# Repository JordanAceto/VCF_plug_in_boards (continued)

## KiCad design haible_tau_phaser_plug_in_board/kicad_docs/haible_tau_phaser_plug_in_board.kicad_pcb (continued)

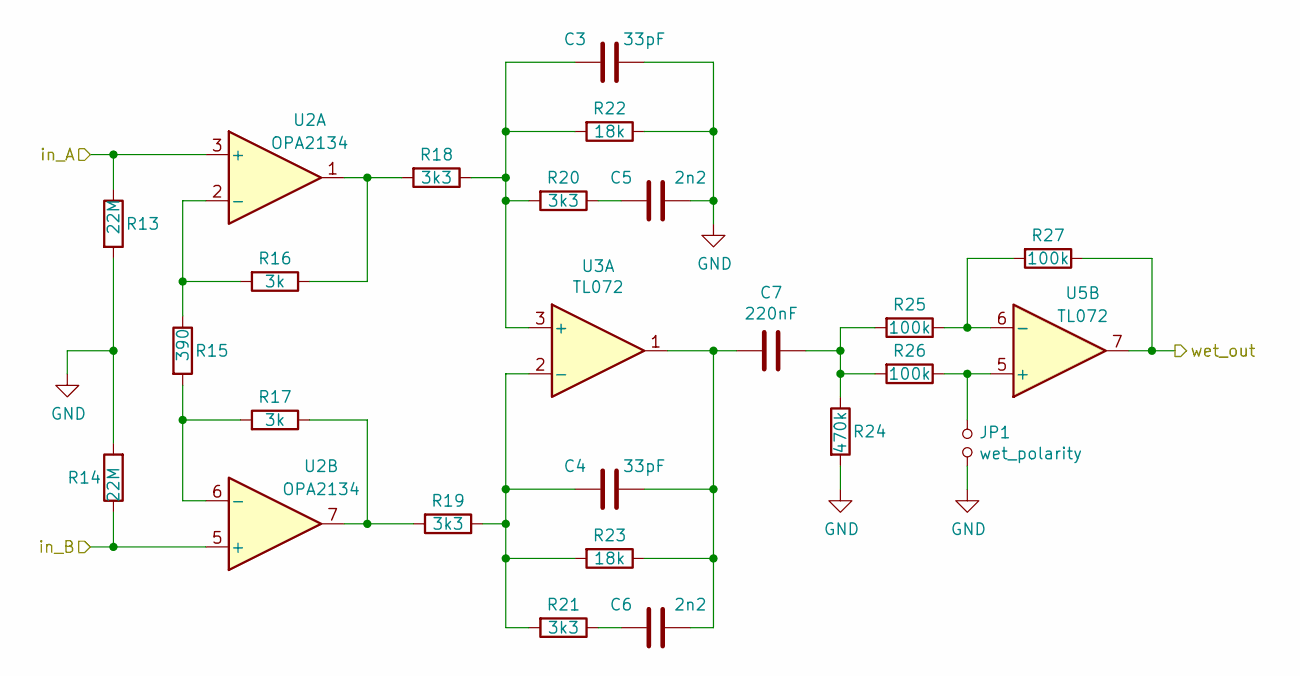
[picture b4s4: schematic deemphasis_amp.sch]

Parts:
C3, C4: 33pF; C_0805_2012Metric_Pad1.15x1.40mm_HandSolder
C5, C6: 2n2; C_0805_2012Metric_Pad1.15x1.40mm_HandSolder
C7: 220nF; C_0805_2012Metric_Pad1.15x1.40mm_HandSolder
JP1: wet_polarity; SolderJumper-2_P1.3mm_Open_Pad1.0x1.5mm
R13, R14: 22M; R_0805_2012Metric_Pad1.15x1.40mm_HandSolder
R15: 390; R_0805_2012Metric_Pad1.15x1.40mm_HandSolder
R16, R17: 3k; R_0805_2012Metric_Pad1.15x1.40mm_HandSolder
R18, R19, R20, R21: 3k3; R_0805_2012Metric_Pad1.15x1.40mm_HandSolder
R22, R23: 18k; R_0805_2012Metric_Pad1.15x1.40mm_HandSolder
R24: 470k; R_0805_2012Metric_Pad1.15x1.40mm_HandSolder
R25, R26, R27: 100k; R_0805_2012Metric_Pad1.15x1.40mm_HandSolder
U2: OPA2134; SOIC-8_3.9x4.9mm_P1.27mm
U3, U5: TL072; SOIC-8_3.9x4.9mm_P1.27mm

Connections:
/cv_processor/control_out_A: R13.1, U2.3 (+); also elsewhere on the board
/cv_processor/control_out_B: R14.1, U2.5 (+); also elsewhere on the board
/feedback_VCA/feedback_signal_in: R27.1, U5.7; also elsewhere on the board
GND: C3.1, C5.1, JP1.2, R13.2, R14.2, R22.1, R24.2; also elsewhere on the board
unnamed: C3.2, R18.1, R20.2, R22.2, U3.3 (+)
unnamed: C4.1, C6.1, C7.2, R23.1, U3.1
unnamed: C4.2, R19.1, R21.2, R23.2, U3.2 (-)
unnamed: C5.2, R20.1
unnamed: C6.2, R21.1
unnamed: C7.1, R24.1, R25.2, R26.2
unnamed: JP1.1, R26.1, U5.5 (+)
unnamed: R15.1, R16.2, U2.2 (-)
unnamed: R15.2, R17.2, U2.6 (-)
unnamed: R16.1, R18.2, U2.1
unnamed: R17.1, R19.2, U2.7
unnamed: R25.1, R27.2, U5.6 (-)

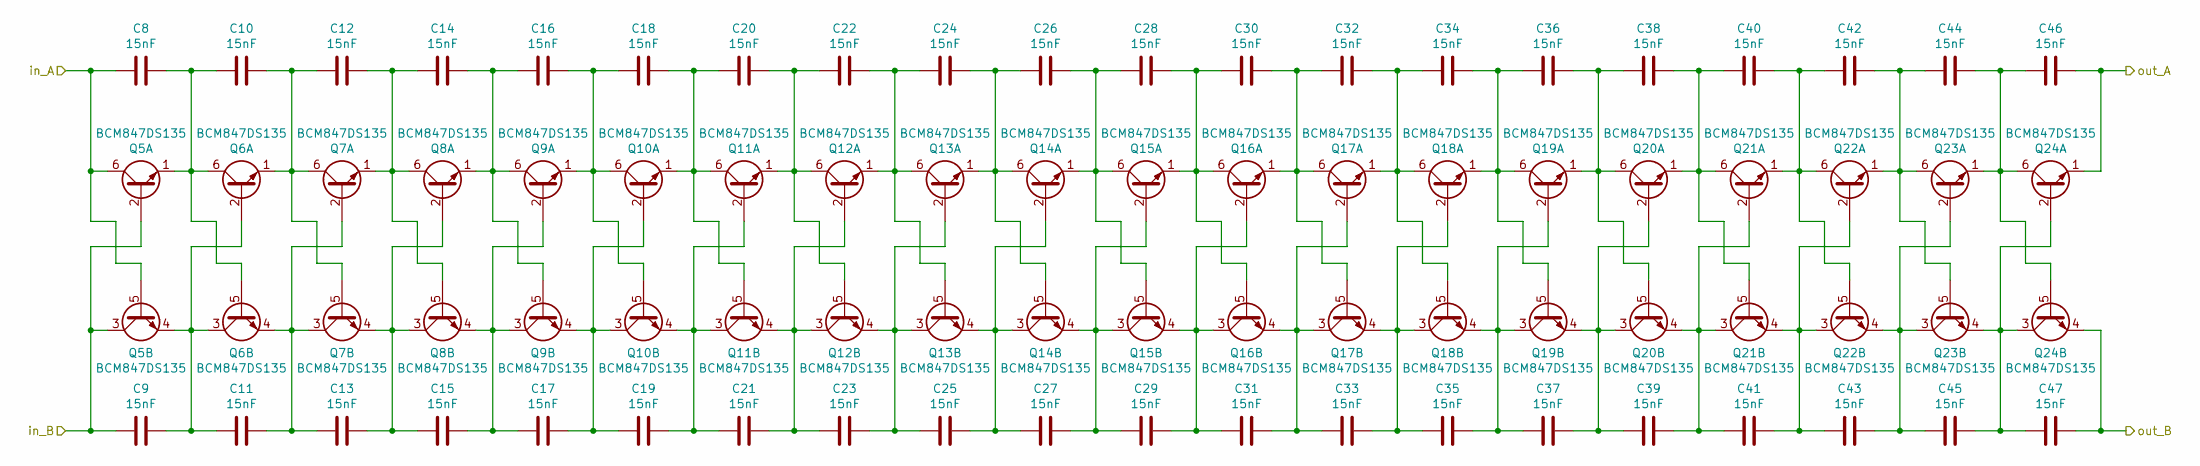
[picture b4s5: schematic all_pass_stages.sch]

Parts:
C8, C9, C10, C11, C12, C13, C14, C15, C16, C17, C18, C19, C20, C21, C22, C23, C24, C25, C26, C27, C28, C29, C30, C31, C32, C33, C34, C35, C36, C37, C38, C39, C40, C41, C42, C43, C44, C45, C46, C47: 15nF; C_0805_2012Metric_Pad1.15x1.40mm_HandSolder
Q5, Q6, Q7, Q8, Q9, Q10, Q11, Q12, Q13, Q14, Q15, Q16, Q17, Q18, Q19, Q20, Q21, Q22, Q23, Q24: BCM847DS135; SOT457

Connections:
/all_pass_stages/in_A: C8.2, Q5.5 (B), Q5.6 (C); also elsewhere on the board
/all_pass_stages/in_B: C9.2, Q5.2 (B), Q5.3 (C); also elsewhere on the board
/cv_processor/control_out_A: C46.1, Q24.1 (E); also elsewhere on the board
/cv_processor/control_out_B: C47.1, Q24.4 (E); also elsewhere on the board
unnamed: C10.1, C12.2, Q6.1 (E), Q7.5 (B), Q7.6 (C)
unnamed: C8.1, C10.2, Q5.1 (E), Q6.5 (B), Q6.6 (C)
unnamed: C11.1, C13.2, Q6.4 (E), Q7.2 (B), Q7.3 (C)
unnamed: C9.1, C11.2, Q5.4 (E), Q6.2 (B), Q6.3 (C)
unnamed: C12.1, C14.2, Q7.1 (E), Q8.5 (B), Q8.6 (C)
unnamed: C13.1, C15.2, Q7.4 (E), Q8.2 (B), Q8.3 (C)
unnamed: C14.1, C16.2, Q8.1 (E), Q9.5 (B), Q9.6 (C)
unnamed: C15.1, C17.2, Q8.4 (E), Q9.2 (B), Q9.3 (C)
unnamed: C16.1, C18.2, Q9.1 (E), Q10.5 (B), Q10.6 (C)
unnamed: C17.1, C19.2, Q9.4 (E), Q10.2 (B), Q10.3 (C)
unnamed: C18.1, C20.2, Q10.1 (E), Q11.5 (B), Q11.6 (C)
unnamed: C19.1, C21.2, Q10.4 (E), Q11.2 (B), Q11.3 (C)
unnamed: C20.1, C22.2, Q11.1 (E), Q12.5 (B), Q12.6 (C)
unnamed: C21.1, C23.2, Q11.4 (E), Q12.2 (B), Q12.3 (C)
unnamed: C22.1, C24.2, Q12.1 (E), Q13.5 (B), Q13.6 (C)
unnamed: C23.1, C25.2, Q12.4 (E), Q13.2 (B), Q13.3 (C)
unnamed: C24.1, C26.2, Q13.1 (E), Q14.5 (B), Q14.6 (C)
unnamed: C25.1, C27.2, Q13.4 (E), Q14.2 (B), Q14.3 (C)
unnamed: C26.1, C28.2, Q14.1 (E), Q15.5 (B), Q15.6 (C)
unnamed: C27.1, C29.2, Q14.4 (E), Q15.2 (B), Q15.3 (C)
unnamed: C28.1, C30.2, Q15.1 (E), Q16.5 (B), Q16.6 (C)
unnamed: C29.1, C31.2, Q15.4 (E), Q16.2 (B), Q16.3 (C)
unnamed: C30.1, C32.2, Q16.1 (E), Q17.5 (B), Q17.6 (C)
unnamed: C31.1, C33.2, Q16.4 (E), Q17.2 (B), Q17.3 (C)
unnamed: C32.1, C34.2, Q17.1 (E), Q18.5 (B), Q18.6 (C)
unnamed: C33.1, C35.2, Q17.4 (E), Q18.2 (B), Q18.3 (C)
unnamed: C34.1, C36.2, Q18.1 (E), Q19.5 (B), Q19.6 (C)
unnamed: C35.1, C37.2, Q18.4 (E), Q19.2 (B), Q19.3 (C)
unnamed: C36.1, C38.2, Q19.1 (E), Q20.5 (B), Q20.6 (C)
unnamed: C37.1, C39.2, Q19.4 (E), Q20.2 (B), Q20.3 (C)
unnamed: C38.1, C40.2, Q20.1 (E), Q21.5 (B), Q21.6 (C)
unnamed: C39.1, C41.2, Q20.4 (E), Q21.2 (B), Q21.3 (C)
unnamed: C40.1, C42.2, Q21.1 (E), Q22.5 (B), Q22.6 (C)
unnamed: C41.1, C43.2, Q21.4 (E), Q22.2 (B), Q22.3 (C)
unnamed: C42.1, C44.2, Q22.1 (E), Q23.5 (B), Q23.6 (C)
unnamed: C43.1, C45.2, Q22.4 (E), Q23.2 (B), Q23.3 (C)
unnamed: C44.1, C46.2, Q23.1 (E), Q24.5 (B), Q24.6 (C)
unnamed: C45.1, C47.2, Q23.4 (E), Q24.2 (B), Q24.3 (C)

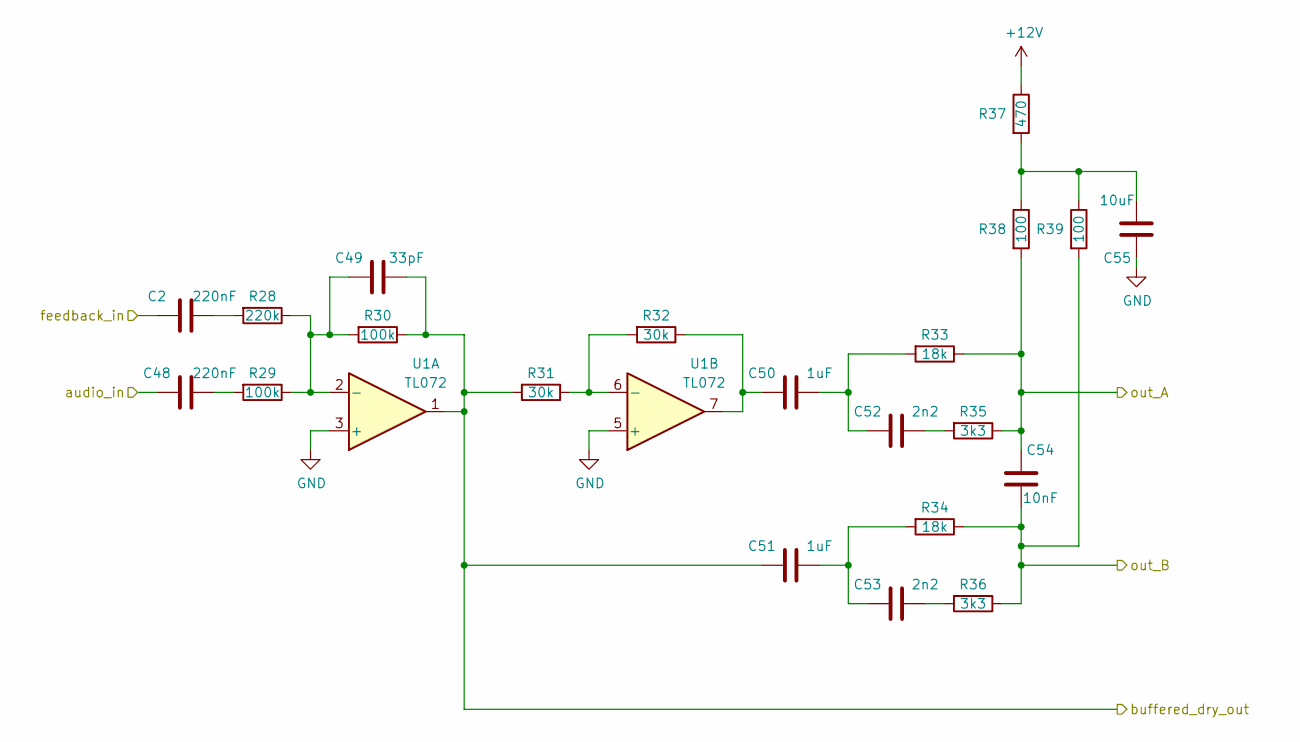
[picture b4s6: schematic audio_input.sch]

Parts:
C2, C48: 220nF; C_0805_2012Metric_Pad1.15x1.40mm_HandSolder
C49: 33pF; C_0805_2012Metric_Pad1.15x1.40mm_HandSolder
C50, C51: 1uF; C_0805_2012Metric_Pad1.15x1.40mm_HandSolder
C52, C53: 2n2; C_0805_2012Metric_Pad1.15x1.40mm_HandSolder
C54: 10nF; C_0805_2012Metric_Pad1.15x1.40mm_HandSolder
C55: 10uF; C_0805_2012Metric_Pad1.15x1.40mm_HandSolder
R28: 220k; R_0805_2012Metric_Pad1.15x1.40mm_HandSolder
R29, R30: 100k; R_0805_2012Metric_Pad1.15x1.40mm_HandSolder
R31, R32: 30k; R_0805_2012Metric_Pad1.15x1.40mm_HandSolder
R33, R34: 18k; R_0805_2012Metric_Pad1.15x1.40mm_HandSolder
R35, R36: 3k3; R_0805_2012Metric_Pad1.15x1.40mm_HandSolder
R37: 470; R_0805_2012Metric_Pad1.15x1.40mm_HandSolder
R38, R39: 100; R_0805_2012Metric_Pad1.15x1.40mm_HandSolder
U1: TL072; SOIC-8_3.9x4.9mm_P1.27mm

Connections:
+12V: R37.1; also elsewhere on the board
/all_pass_stages/in_A: C54.1, R33.1, R35.1, R38.2; also elsewhere on the board
/all_pass_stages/in_B: C54.2, R34.1, R36.1, R39.2; also elsewhere on the board
/audio_input/audio_in: C48.2; also elsewhere on the board
/audio_input/buffered_dry_out: C49.1, C51.2, R30.1, R31.2, U1.1; also elsewhere on the board
/audio_input/feedback_in: C2.2; also elsewhere on the board
GND: C55.2, U1.3 (+), U1.5 (+); also elsewhere on the board
unnamed: C2.1, R28.2
unnamed: C48.1, R29.2
unnamed: C49.2, R28.1, R29.1, R30.2, U1.2 (-)
unnamed: C50.1, C52.2, R33.2
unnamed: C50.2, R32.1, U1.7
unnamed: C51.1, C53.2, R34.2
unnamed: C52.1, R35.2
unnamed: C53.1, R36.2
unnamed: C55.1, R37.2, R38.1, R39.1
unnamed: R31.1, R32.2, U1.6 (-)

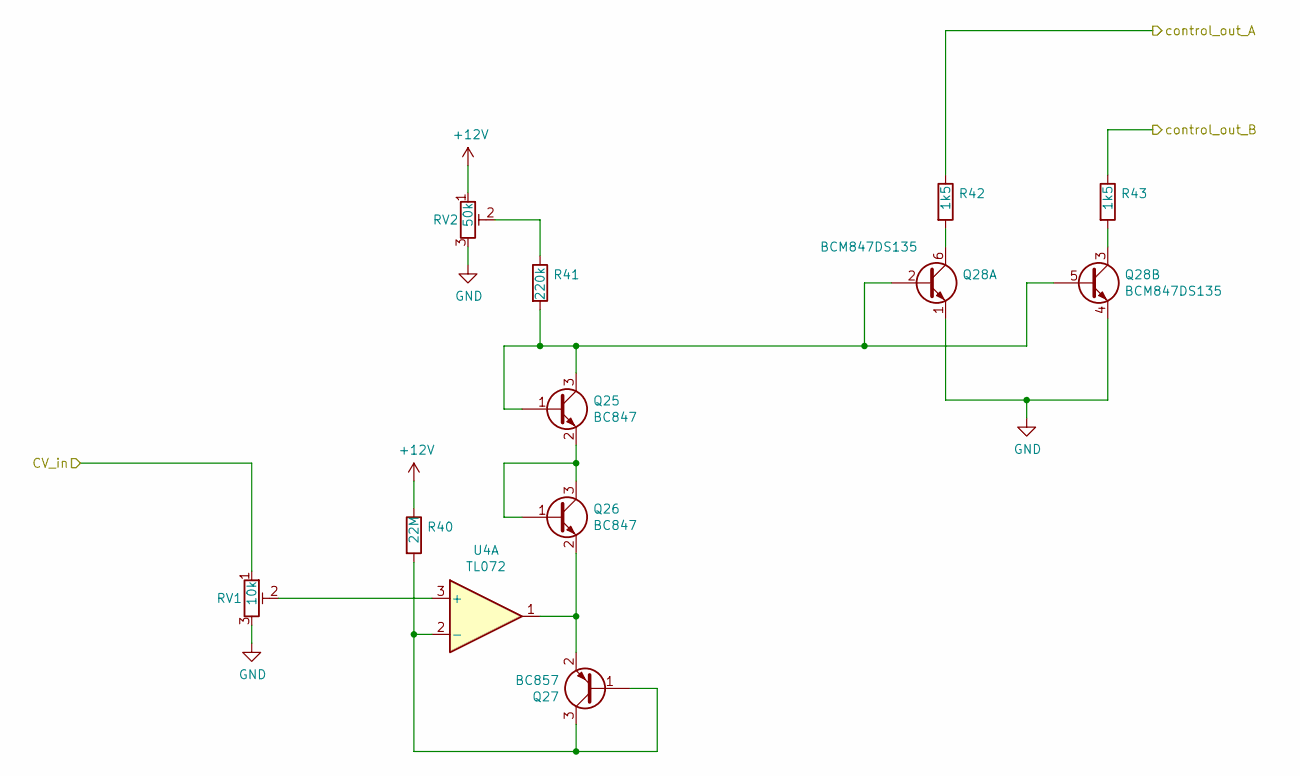
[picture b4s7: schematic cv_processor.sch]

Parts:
Q25, Q26: BC847; SOT-23_Handsoldering
Q27: BC857; SOT-23_Handsoldering
Q28: BCM847DS135; SOT457
R40: 22M; R_0805_2012Metric_Pad1.15x1.40mm_HandSolder
R41: 220k; R_0805_2012Metric_Pad1.15x1.40mm_HandSolder
R42, R43: 1k5; R_0805_2012Metric_Pad1.15x1.40mm_HandSolder
RV1: 10k; Potentiometer_Bourns_3269W_Vertical
RV2: 50k; Potentiometer_Bourns_3269W_Vertical
U4: TL072; SOIC-8_3.9x4.9mm_P1.27mm

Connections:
+12V: R40.1, RV2.1; also elsewhere on the board
/cv_processor/CV_in: RV1.1; also elsewhere on the board
/cv_processor/control_out_A: R42.1; also elsewhere on the board
/cv_processor/control_out_B: R43.1; also elsewhere on the board
GND: Q28.1 (E), Q28.4 (E), RV1.3, RV2.3; also elsewhere on the board
unnamed: Q25.1 (B), Q25.3 (C), Q28.2 (B), Q28.5 (B), R41.2
unnamed: Q25.2 (E), Q26.1 (B), Q26.3 (C)
unnamed: Q26.2 (E), Q27.2 (E), U4.1
unnamed: Q27.1 (B), Q27.3 (C), R40.2, U4.2 (-)
unnamed: Q28.3 (C), R43.2
unnamed: Q28.6 (C), R42.2
unnamed: R41.1, RV2.2
unnamed: RV1.2, U4.3 (+)

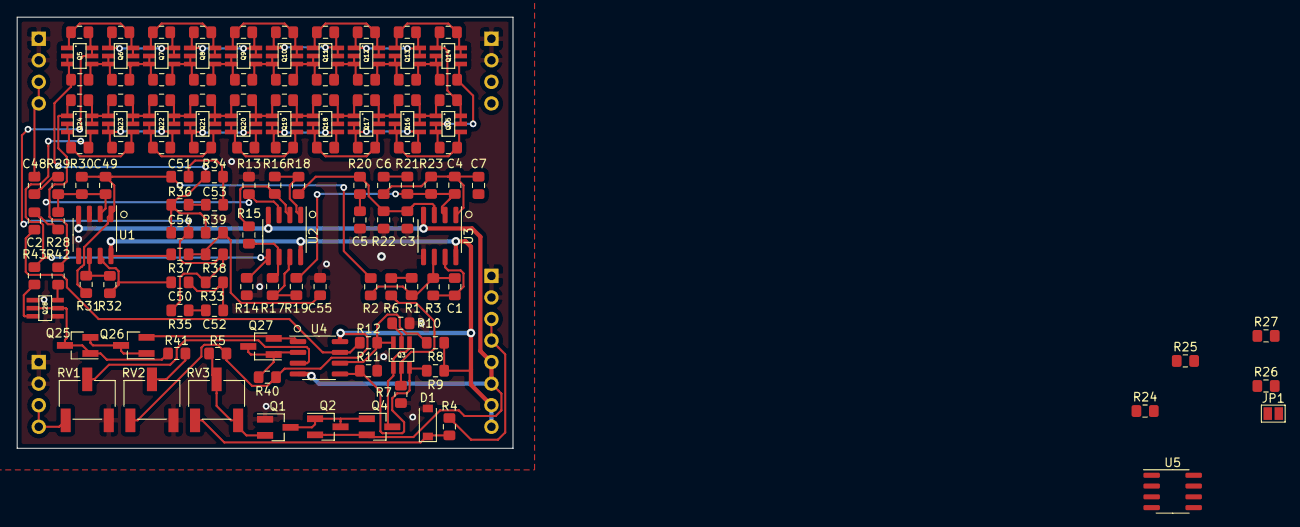
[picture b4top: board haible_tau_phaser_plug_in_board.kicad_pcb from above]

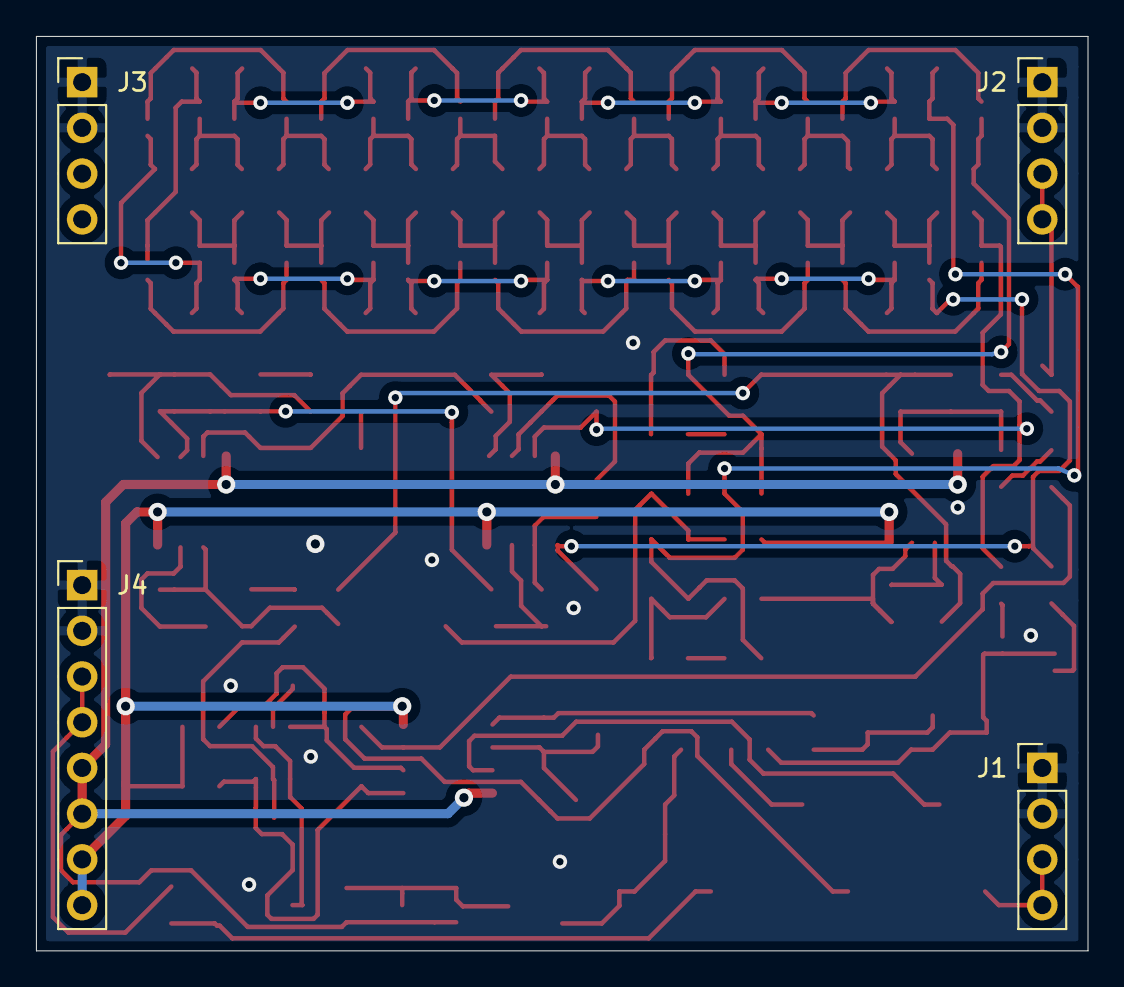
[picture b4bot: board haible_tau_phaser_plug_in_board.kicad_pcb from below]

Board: 2 copper layers, 58.4 x 50.8 mm, 140 parts (4 on the bottom side), 91 nets.

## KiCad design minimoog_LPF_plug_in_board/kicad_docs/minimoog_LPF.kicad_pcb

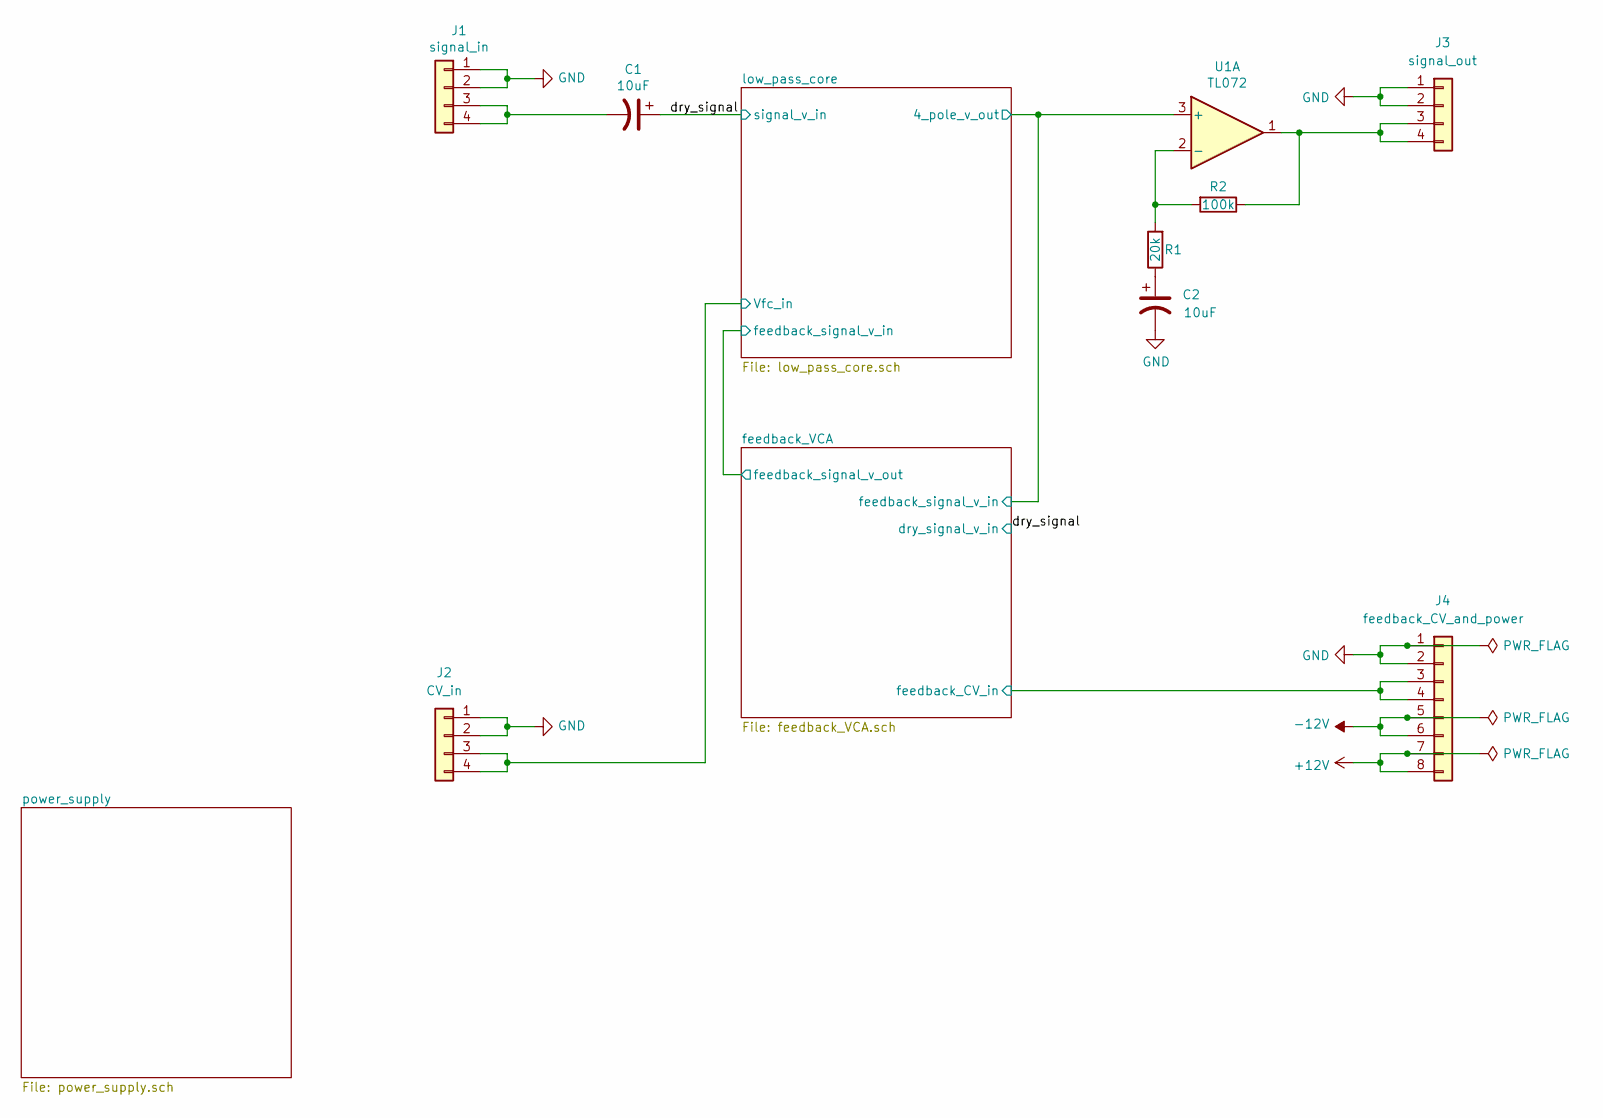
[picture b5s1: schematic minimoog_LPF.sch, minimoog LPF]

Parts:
C1, C2: 10uF; CP_Radial_D6.3mm_P2.50mm
J1: signal_in; PinHeader_1x04_P2.54mm_Vertical
J2: CV_in; PinHeader_1x04_P2.54mm_Vertical
J3: signal_out; PinHeader_1x04_P2.54mm_Vertical
J4: feedback_CV_and_power; PinHeader_1x08_P2.54mm_Vertical
R1: 20k; R_0805_2012Metric_Pad1.15x1.40mm_HandSolder
R2: 100k; R_0805_2012Metric_Pad1.15x1.40mm_HandSolder
U1: TL072; SOIC-8_3.9x4.9mm_P1.27mm

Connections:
+12V: J4.7, J4.8; also elsewhere on the board
-12V: J4.5, J4.6; also elsewhere on the board
/dry_signal: C1.1; also elsewhere on the board
/feedback_VCA/feedback_CV_in: J4.3, J4.4; also elsewhere on the board
/low_pass_core/4_pole_v_out: U1.3 (+); also elsewhere on the board
/low_pass_core/Vfc_in: J2.3, J2.4; also elsewhere on the board
GND: C2.2, J1.1, J1.2, J2.1, J2.2, J3.1, J3.2, J4.1, J4.2; also elsewhere on the board
unnamed: C1.2, J1.3, J1.4
unnamed: C2.1, R1.1
unnamed: J3.3, J3.4, R2.1, U1.1
unnamed: R1.2, R2.2, U1.2 (-)

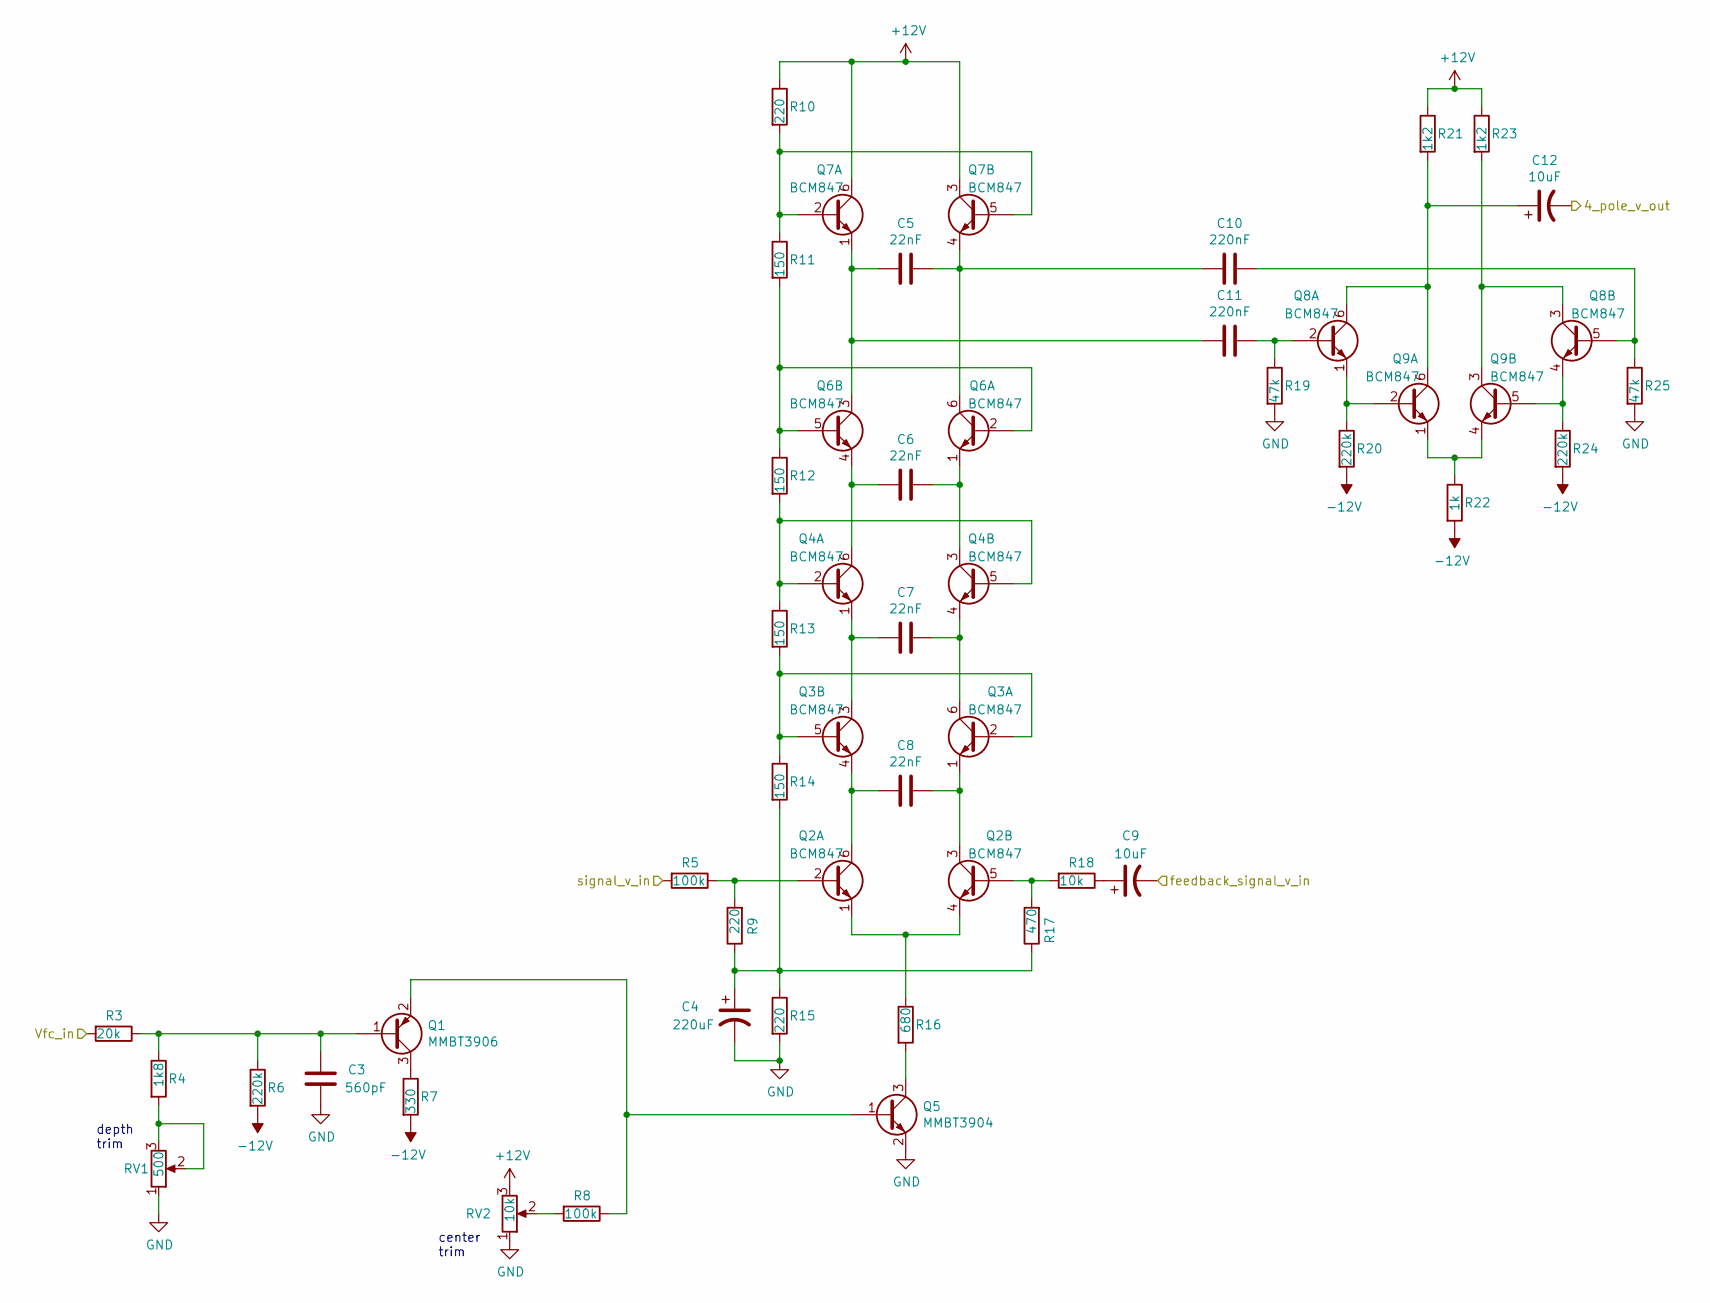
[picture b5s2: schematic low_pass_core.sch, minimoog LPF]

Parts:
C3: 560pF; C_0805_2012Metric_Pad1.15x1.40mm_HandSolder
C4: 220uF; CP_Radial_D6.3mm_P2.50mm
C5, C6, C7, C8: 22nF; C_0805_2012Metric_Pad1.15x1.40mm_HandSolder
C9, C12: 10uF; CP_Radial_D6.3mm_P2.50mm
C10, C11: 220nF; C_Rect_L7.0mm_W3.5mm_P5.00mm
Q1: MMBT3906; SOT-23_Handsoldering
Q2, Q3, Q4, Q6, Q7, Q8, Q9: BCM847; SOT457
Q5: MMBT3904; SOT-23_Handsoldering
R3: 20k; R_0805_2012Metric_Pad1.15x1.40mm_HandSolder
R4: 1k8; R_0805_2012Metric_Pad1.15x1.40mm_HandSolder
R5, R8: 100k; R_0805_2012Metric_Pad1.15x1.40mm_HandSolder
R6, R20, R24: 220k; R_0805_2012Metric_Pad1.15x1.40mm_HandSolder
R7: 330; R_0805_2012Metric_Pad1.15x1.40mm_HandSolder
R9, R10, R15: 220; R_0805_2012Metric_Pad1.15x1.40mm_HandSolder
R11, R12, R13, R14: 150; R_0805_2012Metric_Pad1.15x1.40mm_HandSolder
R16: 680; R_0805_2012Metric_Pad1.15x1.40mm_HandSolder
R17: 470; R_0805_2012Metric_Pad1.15x1.40mm_HandSolder
R18: 10k; R_0805_2012Metric_Pad1.15x1.40mm_HandSolder
R19, R25: 47k; R_0805_2012Metric_Pad1.15x1.40mm_HandSolder
R21, R23: 1k2; R_0805_2012Metric_Pad1.15x1.40mm_HandSolder
R22: 1k; R_0805_2012Metric_Pad1.15x1.40mm_HandSolder
RV1: 500; Potentiometer_Bourns_3296W_Vertical
RV2: 10k; Potentiometer_Bourns_3296W_Vertical

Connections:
+12V: Q7.3 (C), Q7.6 (C), R10.1, R21.1, R23.1, RV2.3; also elsewhere on the board
-12V: R6.2, R7.2, R20.2, R22.2, R24.2; also elsewhere on the board
/dry_signal: R5.2; also elsewhere on the board
/low_pass_core/4_pole_v_out: C12.2; also elsewhere on the board
/low_pass_core/Vfc_in: R3.2; also elsewhere on the board
/low_pass_core/feedback_signal_v_in: C9.2; also elsewhere on the board
GND: C3.1, C4.2, Q5.2 (E), R15.2, R19.2, R25.2, RV1.1, RV2.1; also elsewhere on the board
unnamed: C3.2, Q1.1 (B), R3.1, R4.1, R6.1
unnamed: C4.1, R9.1, R14.2, R15.1, R17.1
unnamed: C6.1, Q4.3 (C), Q6.1 (E)
unnamed: C6.2, Q4.6 (C), Q6.4 (E)
unnamed: C7.1, Q3.6 (C), Q4.4 (E)
unnamed: C7.2, Q3.3 (C), Q4.1 (E)
unnamed: C8.1, Q2.3 (C), Q3.1 (E)
unnamed: C8.2, Q2.6 (C), Q3.4 (E)
unnamed: C9.1, R18.1
unnamed: C10.1, Q8.5 (B), R25.1
unnamed: C5.1, C10.2, Q6.6 (C), Q7.4 (E)
unnamed: C11.1, Q8.2 (B), R19.1
unnamed: C5.2, C11.2, Q6.3 (C), Q7.1 (E)
unnamed: C12.1, Q8.6 (C), Q9.6 (C), R21.2
unnamed: Q1.2 (E), Q5.1 (B), R8.1
unnamed: Q1.3 (C), R7.1
unnamed: Q2.1 (E), Q2.4 (E), R16.1
unnamed: Q2.2 (B), R5.1, R9.2
unnamed: Q2.5 (B), R17.2, R18.2
unnamed: Q3.2 (B), Q3.5 (B), R13.2, R14.1
unnamed: Q4.2 (B), Q4.5 (B), R12.2, R13.1
unnamed: Q5.3 (C), R16.2
unnamed: Q6.2 (B), Q6.5 (B), R11.2, R12.1
unnamed: Q7.2 (B), Q7.5 (B), R10.2, R11.1
unnamed: Q8.1 (E), Q9.2 (B), R20.1
unnamed: Q8.3 (C), Q9.3 (C), R23.2
unnamed: Q8.4 (E), Q9.5 (B), R24.1
unnamed: Q9.1 (E), Q9.4 (E), R22.1
unnamed: R4.2, RV1.2, RV1.3
unnamed: R8.2, RV2.2

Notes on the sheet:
depth trim
center trim

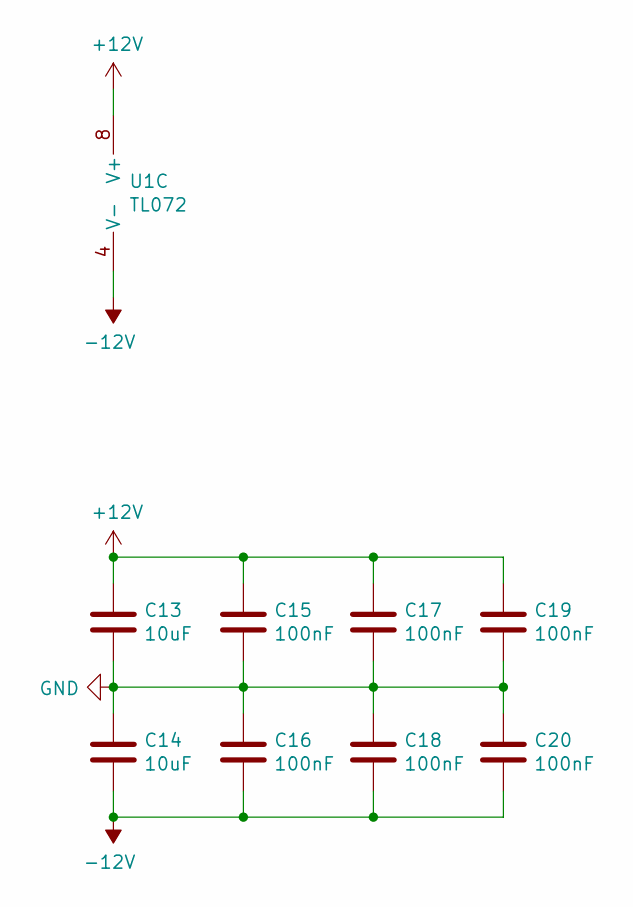
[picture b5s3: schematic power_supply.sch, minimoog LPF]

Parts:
C13, C14: 10uF; C_0805_2012Metric_Pad1.15x1.40mm_HandSolder
C15, C16, C17, C18, C19, C20: 100nF; C_0805_2012Metric_Pad1.15x1.40mm_HandSolder
U1: TL072; SOIC-8_3.9x4.9mm_P1.27mm

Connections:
+12V: C13.1, C15.1, C17.1, C19.1, U1.8 (V+); also elsewhere on the board
-12V: C14.2, C16.2, C18.2, C20.2, U1.4 (V-); also elsewhere on the board
GND: C13.2, C14.1, C15.2, C16.1, C17.2, C18.1, C19.2, C20.1; also elsewhere on the board

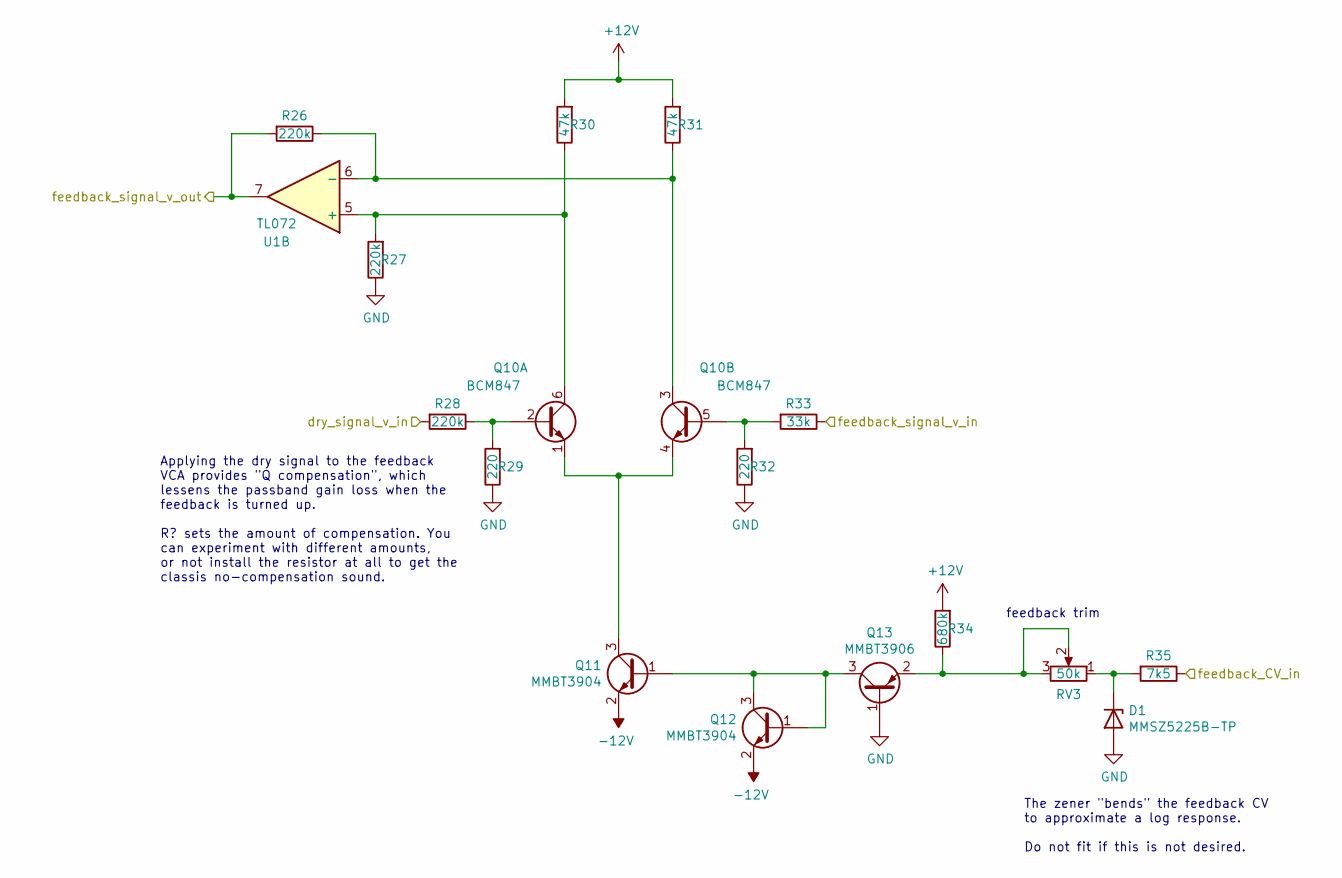
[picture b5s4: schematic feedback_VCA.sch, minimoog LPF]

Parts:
D1: MMSZ5225B-TP; D_SOD-123
Q10: BCM847; SOT457
Q11, Q12: MMBT3904; SOT-23_Handsoldering
Q13: MMBT3906; SOT-23_Handsoldering
R26, R27, R28: 220k; R_0805_2012Metric_Pad1.15x1.40mm_HandSolder
R29, R32: 220; R_0805_2012Metric_Pad1.15x1.40mm_HandSolder
R30, R31: 47k; R_0805_2012Metric_Pad1.15x1.40mm_HandSolder
R33: 33k; R_0805_2012Metric_Pad1.15x1.40mm_HandSolder
R34: 680k; R_0805_2012Metric_Pad1.15x1.40mm_HandSolder
R35: 7k5; R_0805_2012Metric_Pad1.15x1.40mm_HandSolder
RV3: 50k; Potentiometer_Bourns_3296W_Vertical
U1: TL072; SOIC-8_3.9x4.9mm_P1.27mm

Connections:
+12V: R30.2, R31.2, R34.2; also elsewhere on the board
-12V: Q11.2 (E), Q12.2 (E); also elsewhere on the board
/dry_signal: R28.2; also elsewhere on the board
/feedback_VCA/feedback_CV_in: R35.1; also elsewhere on the board
/low_pass_core/4_pole_v_out: R33.1; also elsewhere on the board
/low_pass_core/feedback_signal_v_in: R26.2, U1.7; also elsewhere on the board
GND: D1.2 (A), Q13.1 (B), R27.1, R29.1, R32.1; also elsewhere on the board
unnamed: D1.1 (K), R35.2, RV3.1
unnamed: Q10.1 (E), Q10.4 (E), Q11.3 (C)
unnamed: Q10.2 (B), R28.1, R29.2
unnamed: Q10.3 (C), R26.1, R31.1, U1.6 (-)
unnamed: Q10.5 (B), R32.2, R33.2
unnamed: Q10.6 (C), R27.2, R30.1, U1.5 (+)
unnamed: Q11.1 (B), Q12.1 (B), Q12.3 (C), Q13.3 (C)
unnamed: Q13.2 (E), R34.1, RV3.2, RV3.3

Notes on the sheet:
The zener "bends" the feedback CV to approximate a log response. Do not fit if this is not desired.
feedback trim
Applying the dry signal to the feedback VCA provides "Q compensation", which lessens the passband gain loss when the feedback is turned up. R? sets the amount of compensation. You can experiment with different amounts, or not install the resistor at all to get the classis no-compensation sound.

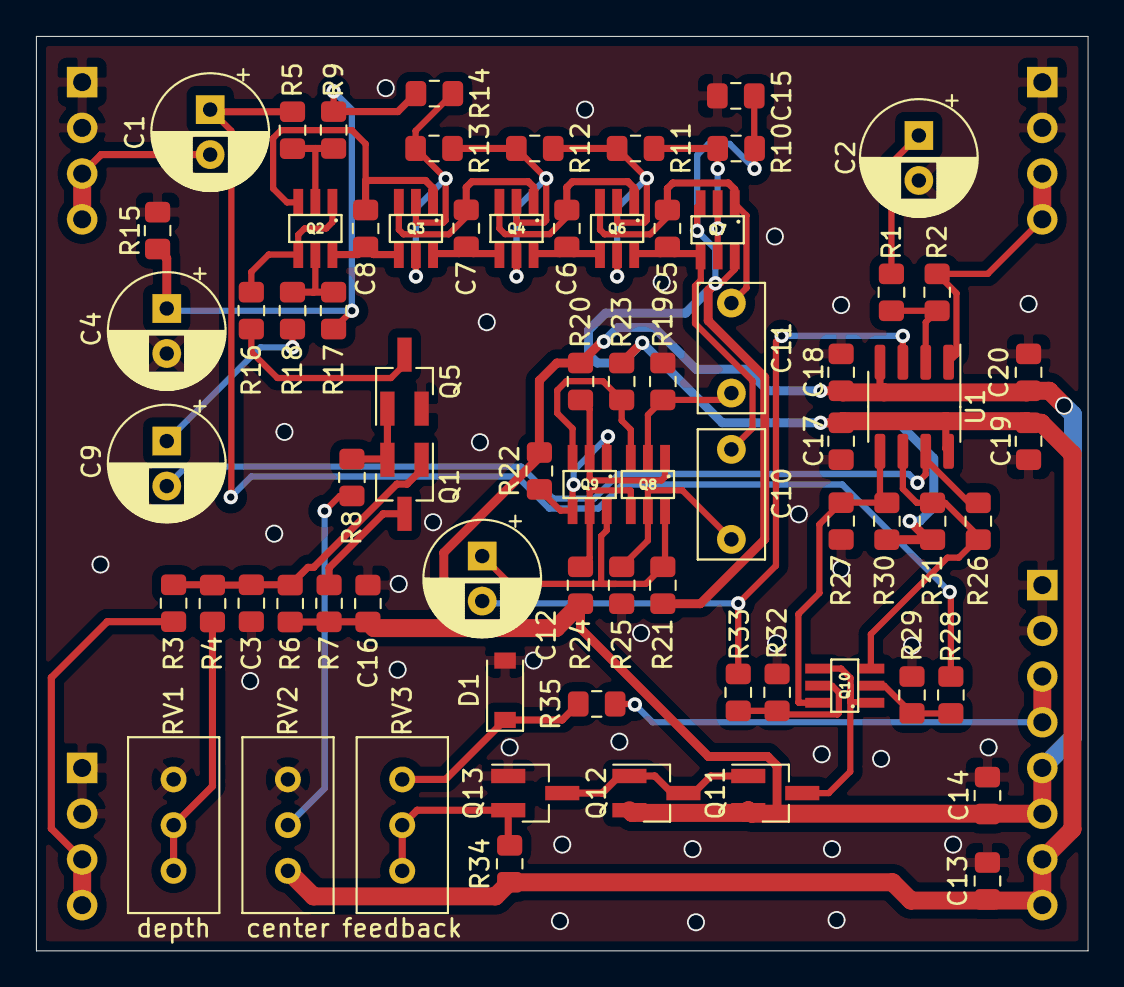
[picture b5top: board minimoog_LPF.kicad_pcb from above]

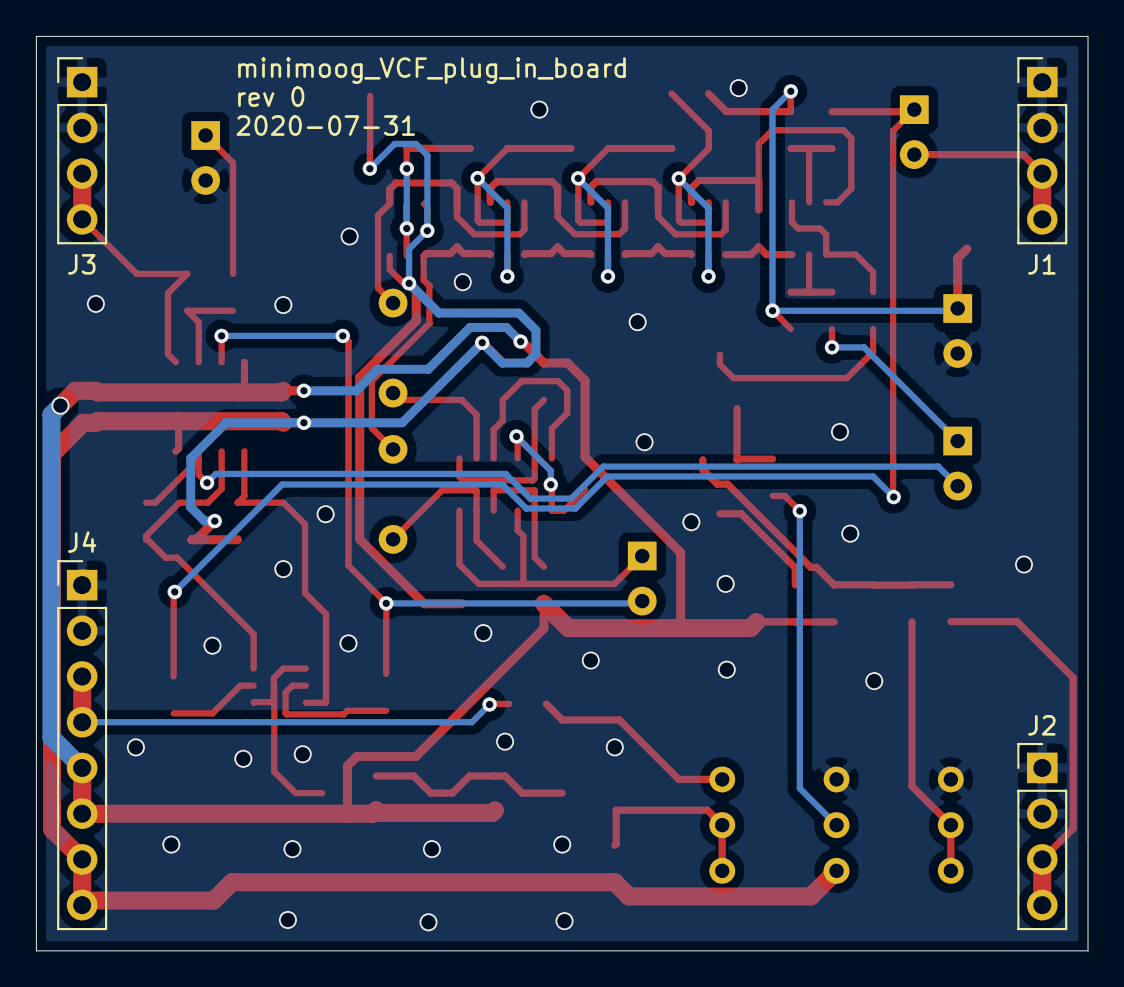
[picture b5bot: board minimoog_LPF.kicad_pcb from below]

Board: 2 copper layers, 58.4 x 50.8 mm, 77 parts (4 on the bottom side), 50 nets.
